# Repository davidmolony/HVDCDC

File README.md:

# HVDCDC
Hardware and firmware for stm32G030F6 based DCDC converter

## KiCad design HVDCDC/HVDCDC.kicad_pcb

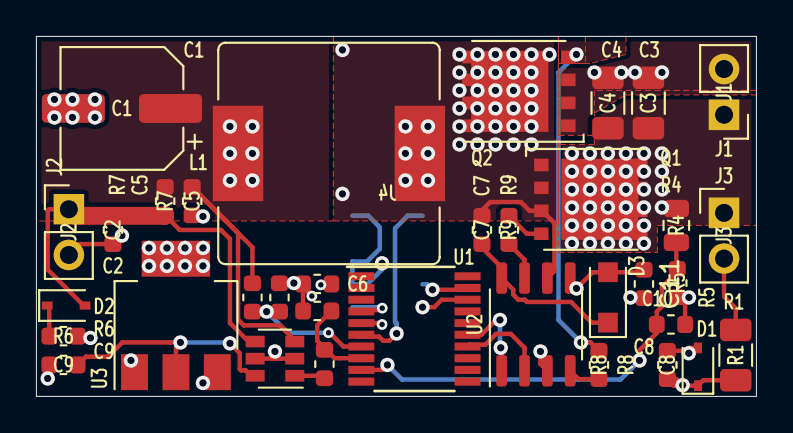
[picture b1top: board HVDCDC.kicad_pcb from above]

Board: 4 copper layers, 40.0 x 20.0 mm, 36 parts (1 on the bottom side), 23 nets.

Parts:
C1: C_100uF 35V elec; CP_Elec_6.3x7.7
C2, C5, C6, C7, C8, C9, C11: C_10uF 25V; C_0603_1608Metric
C3, C4: C_2.2uF 100V; C_1206_3216Metric
C10, C12: C_10nF 25V; C_0603_1608Metric
D1, D2: D_Zener; D_SOD-323
D3: D_Small; D_SOD-123F
J1, J2, J3: Conn_01x02_Male; PinHeader_1x02_P2.54mm_Vertical
J4: Conn_ARM_JTAG_SWD_10; PinHeader_2x05_P1.27mm_Vertical_SMD
L1: L_Small; L_Bourns_SRR1210A
Q1, Q2: BSC105N10LSFG; TDSON-8-1
R1: R_10K; R_1206_3216Metric
R2: R_2.2k; R_0603_1608Metric
R3, R5: R_10k; R_0603_1608Metric
R4: R_1M; R_0805_2012Metric
R6, R10: R_47; R_0603_1608Metric
R7: R_10mR; R_0603_1608Metric
R8, R9: R_4.7; R_0603_1608Metric
U1: STM32G030F6Px; TSSOP-20_4.4x6.5mm_P0.65mm
U2: IR2181; SO-8_3.9x4.9mm_P1.27mm
U3: AMS1117-3.3; SOT-223-3_TabPin2
U4: INA180A2 (G50); SOT-23-6

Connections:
+3V3: C6.1, C9.1, J4.1, U1.4, U3.2, U4.6
+12V: C8.1, C11.1, D1.1, D3.2, R1.2, R6.2, U2.5, U3.3
+BATT: C3.1, C4.1, J1.1, J3.1, Q1.5, R4.1
+VDC: C2.1, D2.2, J2.1, R7.2, U4.4
/Hin: U1.15, U2.1
/IoutFB: R10.2, U4.1
/Lin: U1.14, U2.2
/SWCLK: J4.4, U1.19
/SWDIO: J4.2, U1.18
/SwitchNode: C7.2, L1.1, Q1.1, Q1.2, Q1.3, Q2.5, U2.6
/VinFB: C10.1, R4.2, R5.2, U1.9
/Vout+: C1.1, C5.1, L1.2, R3.1, R7.1, U4.3
/VoutFB: R2.1, R3.2, U1.7
/nRst: J4.10, U1.6
GND: C1.2, C2.2, C3.2, C4.2, C5.2, C6.2, C8.2, C9.2, C10.2, C11.2, C12.2, D1.2, J1.2, J2.2, J4.3, J4.5, J4.9, Q2.1, Q2.2, Q2.3, R2.2, R5.1, U1.5, U2.3, U3.1, U4.2, U4.5
unnamed: C7.1, D3.1, U2.8
unnamed: C12.1, R10.1, U1.8
unnamed: D2.1, R6.1
unnamed: J3.2, R1.1
unnamed: Q1.4, R9.2
unnamed: Q2.4, R8.2
unnamed: R8.1, U2.4
unnamed: R9.1, U2.7

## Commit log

2022-10-10 Working ADC reads, PWM and interrupts
2023-01-25 Add hardware files
2023-01-25 Commit pre merging hardware
2023-01-25 Working code for HVDCDC
2023-01-31 Small changes to make this run at 90V
